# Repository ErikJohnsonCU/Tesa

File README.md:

Tesa
====

Working board design and firmware for Tesa
==========================================

Please note I mis-ordered the 10k resistors as 2k resistors, these will still work as the value of the pull-up resistors on the reset line is very flexible.

Touch pads are numbered as follows:
Power -> 1
Micro -> 2
Accel -> 3
Touch -> 4

Leds are numbered as follows:
Micro -> 0 (rgb positions to be added)
Power -> 1 (rgb positions to be added)
Accel -> 2 (rgb positions to be added)
Touch -> 3 (rgb positions to be added)
r=3,g=2,b=1

Jumper resistor functions:
R105: connects PWRIN pin + to POWER pin 1 (use this to power uC via POWER header or distribute PWRIN pin + to other boards)
RECALL: POWER pin 1 drives LEDs
R108: connects POWER pin 3 to board's Vcc (+3.3V) (use this to run uC off external +3.3V or distribute +3.3V to other boards)

Similar work by other OH designers:
http://www.ofbrooklyn.com/2014/09/6/building-pulse-bloom-biofeedback-burning-man-2014/

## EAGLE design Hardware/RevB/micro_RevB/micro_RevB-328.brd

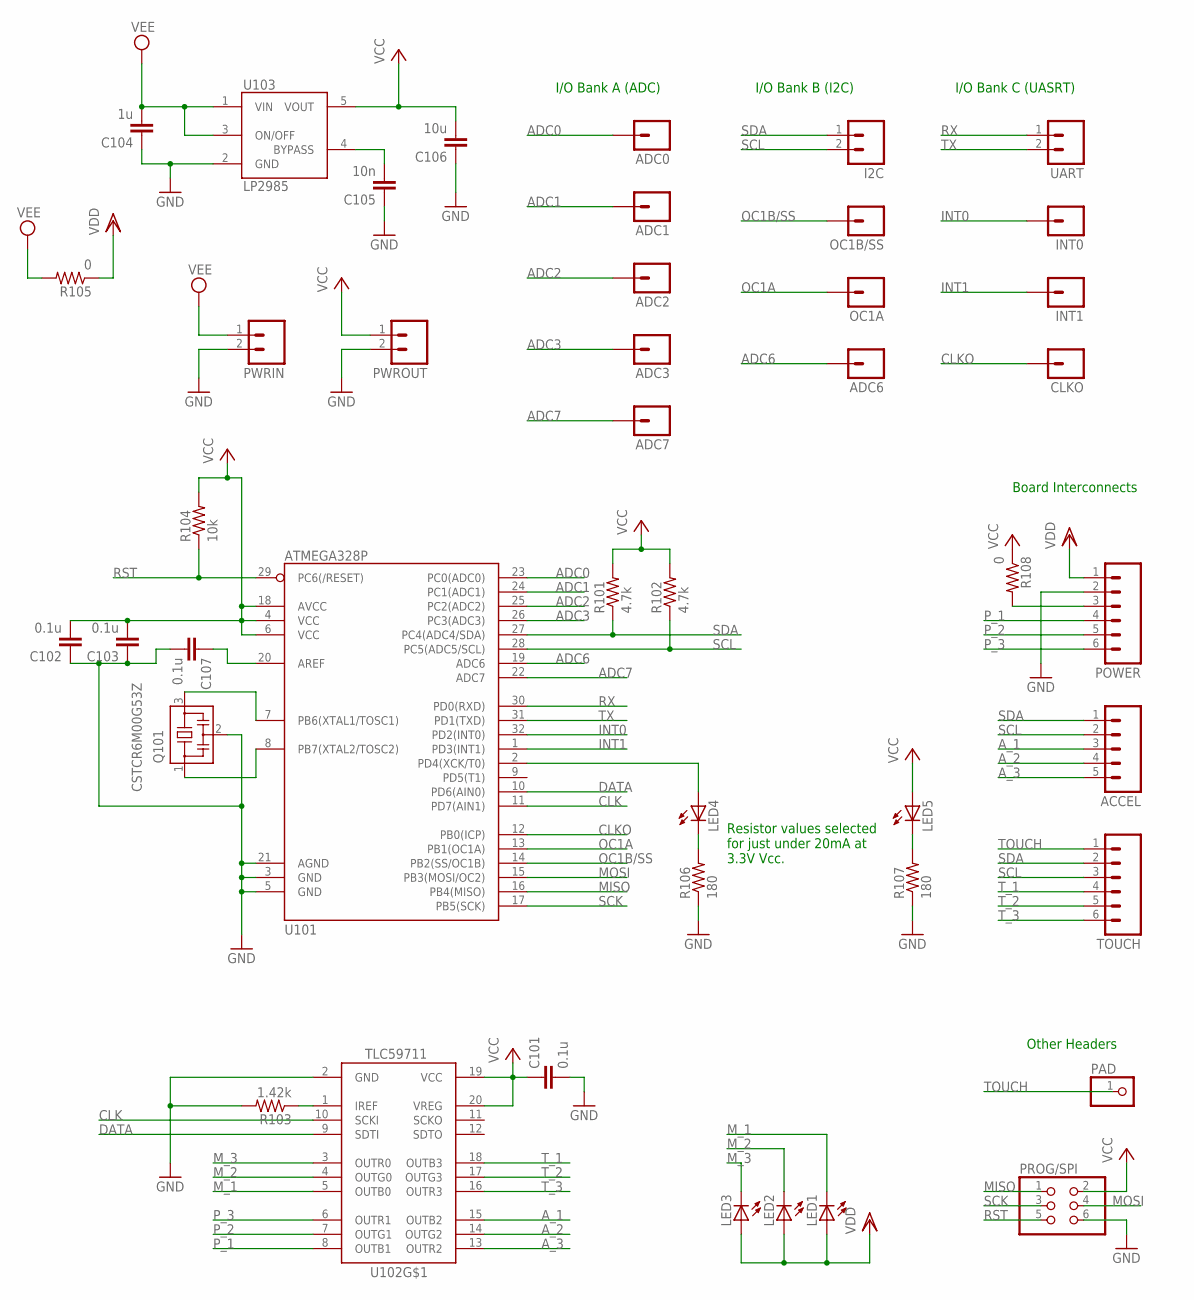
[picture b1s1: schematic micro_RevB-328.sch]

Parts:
ACCEL: M05LOCK; 1X05_LOCK
ADC0, ADC1, ADC2, ADC3, ADC6, ADC7: M01PTH; 1X01
C101, C102, C103, C107: 0.1u; C0603
C104: 1u; C0603
C105: 10n; C0603
C106: 10u; C0603
CLKO: M01PTH; 1X01
I2C: M02LOCK; 1X02_LOCK
INT0, INT1: M01PTH; 1X01
LED1, LED2, LED3: LEDP-LCC-4; P-LCC-4
LED4, LED5: LEDSML0603; SML0603
OC1A, OC1B/SS: M01PTH; 1X01
PAD: PINHD-1X1; 1X01
POWER: M06SIP_LOCK; 1X06-SIP_LOCK
PROG/SPI: PINHD-2X3; 2X03
PWRIN: M02LOCK; 1X02_LOCK
PWROUT: M02LOCK; 1X02_LOCK
Q101: CSTCR6M00G53Z; CSTCR6M
R101, R102: 4.7k; R0603
R103: 1.42k; R0603
R104: 10k; R0603
R105, R108: 0; R0603
R106, R107: 180; R0603
TOUCH: M06SIP_LOCK; 1X06-SIP_LOCK
U101: ATMEGA328P; TQFP32-08
U102: TLC59711; HTSSOP20DAP
U103: LP2985AIM5-3.3; SOT25
UART: M02LOCK; 1X02_LOCK

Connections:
ADC0: ADC0.1, U101.23 (PC0(ADC0))
ADC1: ADC1.1, U101.24 (PC1(ADC1))
ADC2: ADC2.1, U101.25 (PC2(ADC2))
ADC3: ADC3.1, U101.26 (PC3(ADC3))
ADC6: ADC6.1, U101.19 (ADC6)
ADC7: ADC7.1, U101.22 (ADC7)
A_1: ACCEL.3, U102.15 (OUTB2)
A_2: ACCEL.4, U102.14 (OUTG2)
A_3: ACCEL.5, U102.13 (OUTR2)
BYPASS: C105.2, U103.4 (BYPASS)
CLK: U101.11 (PD7(AIN1)), U102.10 (SCKI)
CLKO: CLKO.1, U101.12 (PB0(ICP))
DATA: U101.10 (PD6(AIN0)), U102.9 (SDTI)
INT0: INT0.1, U101.32 (PD2(INT0))
INT1: INT1.1, U101.1 (PD3(INT1))
MISO: PROG/SPI.1, U101.16 (PB4(MISO))
MOSI: PROG/SPI.4, U101.15 (PB3(MOSI/OC2))
M_1: LED1.C@4 (C), U102.5 (OUTB0)
M_2: LED2.C@4 (C), U102.4 (OUTG0)
M_3: LED3.C@4 (C), U102.3 (OUTR0)
N7: C101.2, C102.1, C103.1, C104.1, C105.1, C106.1, C107.2, POWER.2, PROG/SPI.6, PWRIN.2, PWROUT.2, Q101.2, R103.2, R106.1, R107.1, U101.3 (GND), U101.5 (GND), U101.21 (AGND), U102.2 (GND), U103.2 (GND)
unnamed: Q101.1, U101.8 (PB7(XTAL2/TOSC2))
unnamed: Q101.3, U101.7 (PB6(XTAL1/TOSC1))
unnamed: LED4.A, U101.2 (PD4(XCK/T0))
unnamed: R103.1, U102.1 (IREF)
unnamed: POWER.3, R108.2
unnamed: LED4.C, R106.2
unnamed: C107.1, U101.20 (AREF)
unnamed: LED5.C, R107.2
OC1A: OC1A.1, U101.13 (PB1(OC1A))
OC1B/SS: OC1B/SS.1, U101.14 (PB2(SS/OC1B))
P_1: POWER.4, U102.8 (OUTB1)
P_2: POWER.5, U102.7 (OUTG1)
P_3: POWER.6, U102.6 (OUTR1)
RST: PROG/SPI.5, R104.1, U101.29 (PC6(/RESET))
RX: U101.30 (PD0(RXD)), UART.1
SCK: PROG/SPI.3, U101.17 (PB5(SCK))
SCL: ACCEL.2, I2C.2, R102.1, TOUCH.3, U101.28 (PC5(ADC5/SCL))
SDA: ACCEL.1, I2C.1, R101.1, TOUCH.2, U101.27 (PC4(ADC4/SDA))
TOUCH: PAD.1, TOUCH.1
TX: U101.31 (PD1(TXD)), UART.2
T_1: TOUCH.4, U102.18 (OUTB3)
T_2: TOUCH.5, U102.17 (OUTG3)
T_3: TOUCH.6, U102.16 (OUTR3)
VCC: C101.1, C102.2, C103.2, C106.2, LED5.A, PROG/SPI.2, PWROUT.1, R101.2, R102.2, R104.2, R108.1, U101.4 (VCC), U101.6 (VCC), U101.18 (AVCC), U102.19 (VCC), U102.20 (VREG), U103.5 (VOUT)
VDD: LED1.A, LED2.A, LED3.A, POWER.1, R105.1
VEE: C104.2, PWRIN.1, R105.2, U103.1 (VIN), U103.3 (ON/OFF)

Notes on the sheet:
I/O Bank A (ADC)
I/O Bank B (I2C)
I/O Bank C (UASRT)
Resistor values selected for just under 20mA at 3.3V Vcc.
Board Interconnects
Other Headers

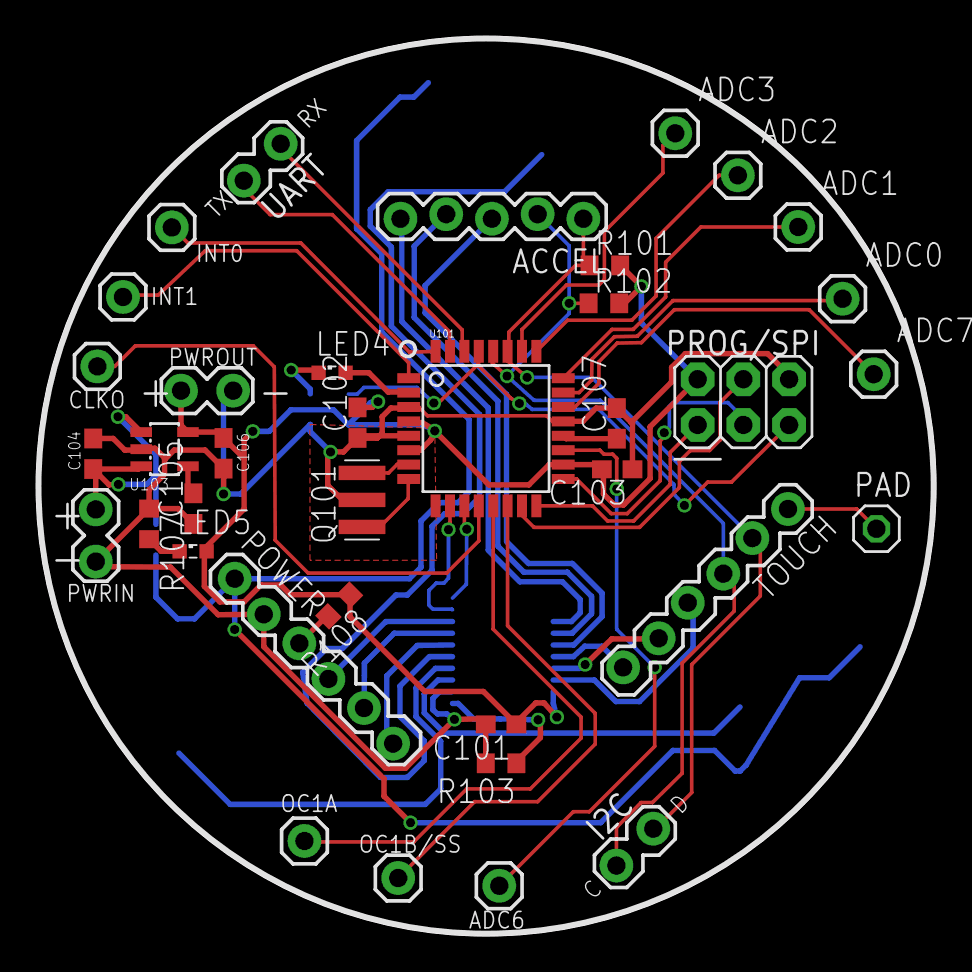
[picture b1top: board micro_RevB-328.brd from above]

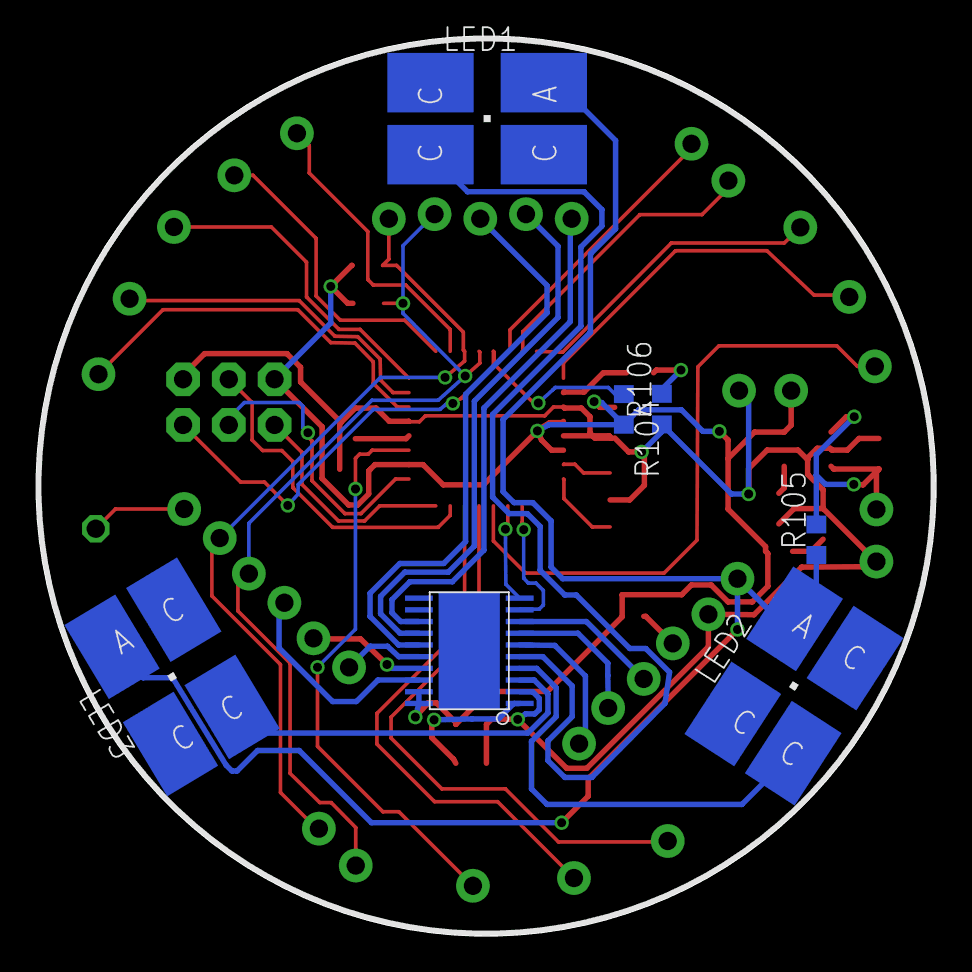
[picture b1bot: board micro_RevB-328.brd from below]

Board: 2 copper layers, 50.0 x 50.0 mm, 44 parts (7 on the bottom side), 47 nets.

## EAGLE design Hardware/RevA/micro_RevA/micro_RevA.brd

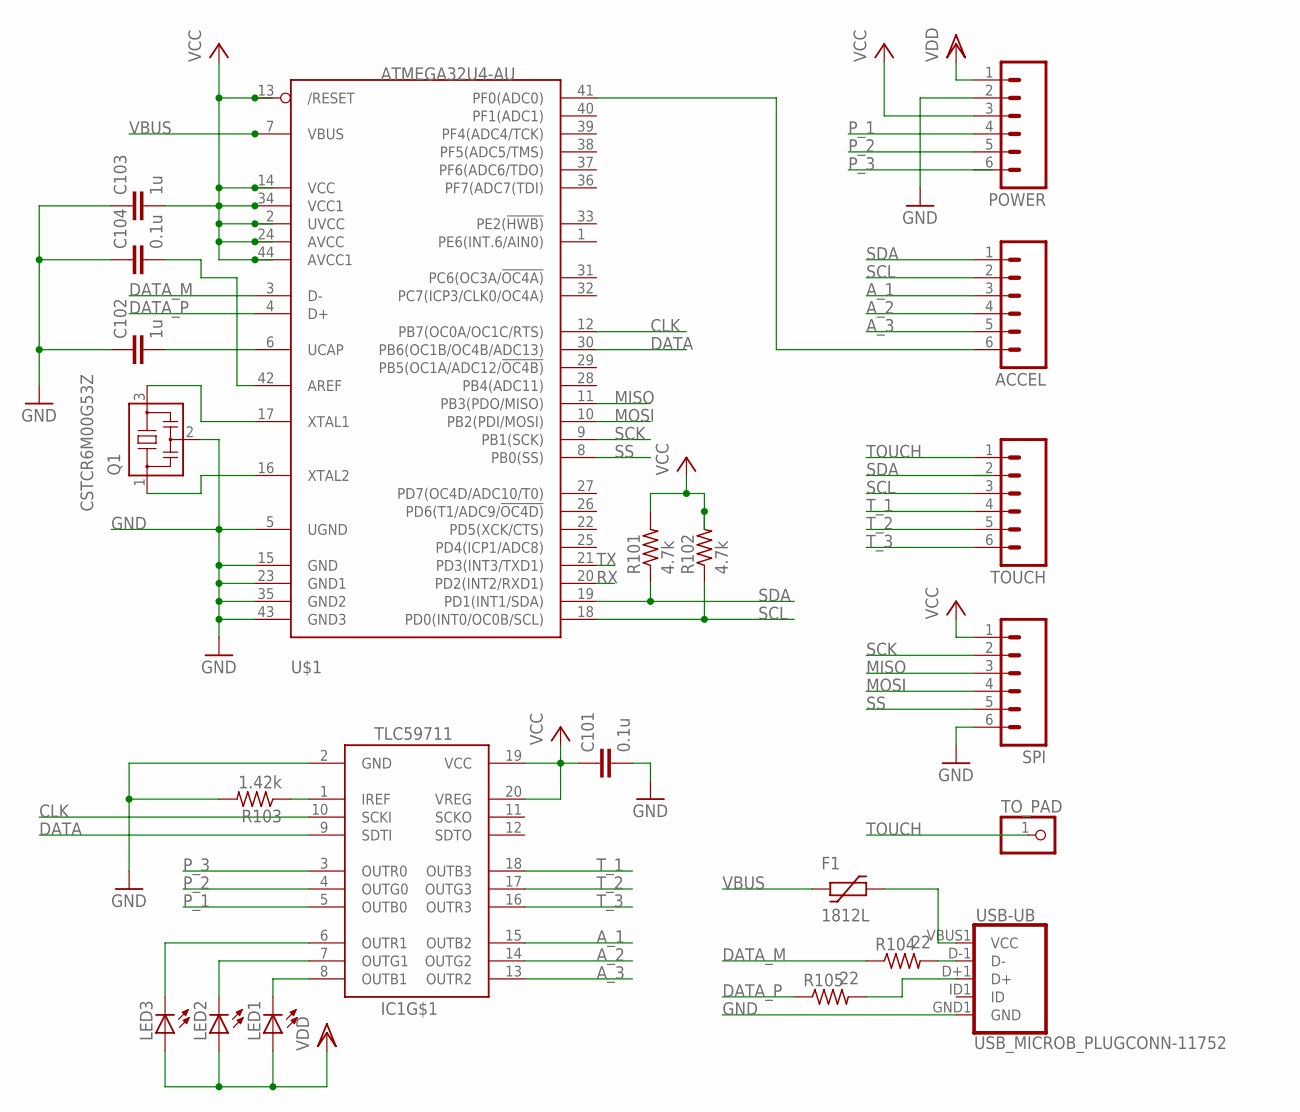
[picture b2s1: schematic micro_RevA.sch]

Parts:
ACCEL: M06SMD-STRAIGHT-ALT; 1X06_SMD_STRAIGHT_ALT
C101, C104: 0.1u; C0603
C102, C103: 1u; C0603
F1: 1812L
IC1: TLC59711; HTSSOP20DAP
LED1, LED2, LED3: LEDP-LCC-4; P-LCC-4
POWER: M06SMD-STRAIGHT-ALT; 1X06_SMD_STRAIGHT_ALT
Q1: CSTCR6M00G53Z; CSTCR6M
R101, R102: 4.7k; R0603
R103: 1.42k; R0603
R104, R105: 22; R0603
SPI: M06SMD-STRAIGHT-ALT; 1X06_SMD_STRAIGHT_ALT
TOUCH: M06SMD-STRAIGHT-ALT; 1X06_SMD_STRAIGHT_ALT
TO_PAD: PINHD-1X1; 1X01
U$1: ATMEGA32U4-AU; TQFP44
USB-UB: USB_MICROB_PLUGCONN-11752; USB-B-MICRO-SMD_V03

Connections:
A_1: ACCEL.3, IC1.15 (OUTB2)
A_2: ACCEL.4, IC1.14 (OUTG2)
A_3: ACCEL.5, IC1.13 (OUTR2)
CLK: IC1.10 (SCKI), U$1.12 (PB7(OC0A/OC1C/RTS))
DATA: IC1.9 (SDTI), U$1.30 (PB6(OC1B/OC4B/ADC13))
DATA_M: R104.1, U$1.3 (D-)
DATA_P: R105.1, U$1.4 (D+)
GND: C101.2, C102.1, C103.1, C104.1, IC1.2 (GND), POWER.2, Q1.2, R103.2, SPI.6, U$1.5 (UGND), U$1.15 (GND), U$1.23 (GND1), U$1.35 (GND2), U$1.43 (GND3), USB-UB.GND1 (GND)
MISO: SPI.3, U$1.11 (PB3(PDO/MISO))
MOSI: SPI.4, U$1.10 (PB2(PDI/MOSI))
unnamed: Q1.3, U$1.17 (XTAL1)
unnamed: Q1.1, U$1.16 (XTAL2)
unnamed: C104.2, U$1.42 (AREF)
unnamed: IC1.1 (IREF), R103.1
unnamed: IC1.6 (OUTR1), LED3.C@4 (C)
unnamed: IC1.7 (OUTG1), LED2.C@4 (C)
unnamed: IC1.8 (OUTB1), LED1.C@4 (C)
unnamed: C102.2, U$1.6 (UCAP)
unnamed: ACCEL.6, U$1.41 (PF0(ADC0))
unnamed: R104.2, USB-UB.D-1 (D-)
unnamed: R105.2, USB-UB.D+1 (D+)
unnamed: F1.P$2 (2), USB-UB.VBUS1 (VCC)
P_1: IC1.5 (OUTB0), POWER.4
P_2: IC1.4 (OUTG0), POWER.5
P_3: IC1.3 (OUTR0), POWER.6
RX: U$1.20 (PD2(INT2/RXD1))
SCK: SPI.2, U$1.9 (PB1(SCK))
SCL: ACCEL.2, R102.1, TOUCH.3, U$1.18 (PD0(INT0/OC0B/SCL))
SDA: ACCEL.1, R101.1, TOUCH.2, U$1.19 (PD1(INT1/SDA))
SS: SPI.5, U$1.8 (PB0(SS))
TOUCH: TOUCH.1, TO_PAD.1
TX: U$1.21 (PD3(INT3/TXD1))
T_1: IC1.18 (OUTB3), TOUCH.4
T_2: IC1.17 (OUTG3), TOUCH.5
T_3: IC1.16 (OUTR3), TOUCH.6
VBUS: F1.P$1 (1), U$1.7 (VBUS)
VCC: C101.1, C103.2, IC1.19 (VCC), IC1.20 (VREG), POWER.3, R101.2, R102.2, SPI.1, U$1.2 (UVCC), U$1.13 (/RESET), U$1.14 (VCC), U$1.24 (AVCC), U$1.34 (VCC1), U$1.44 (AVCC1)
VDD: LED1.A, LED2.A, LED3.A, POWER.1

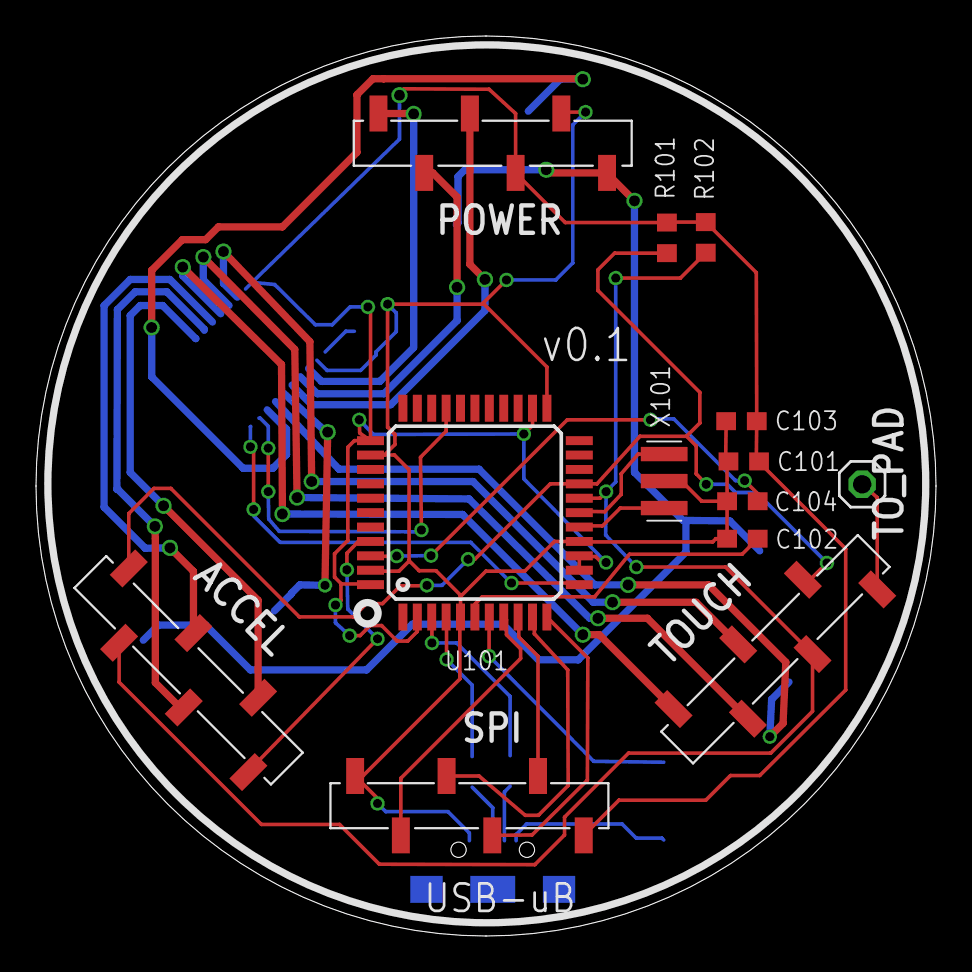
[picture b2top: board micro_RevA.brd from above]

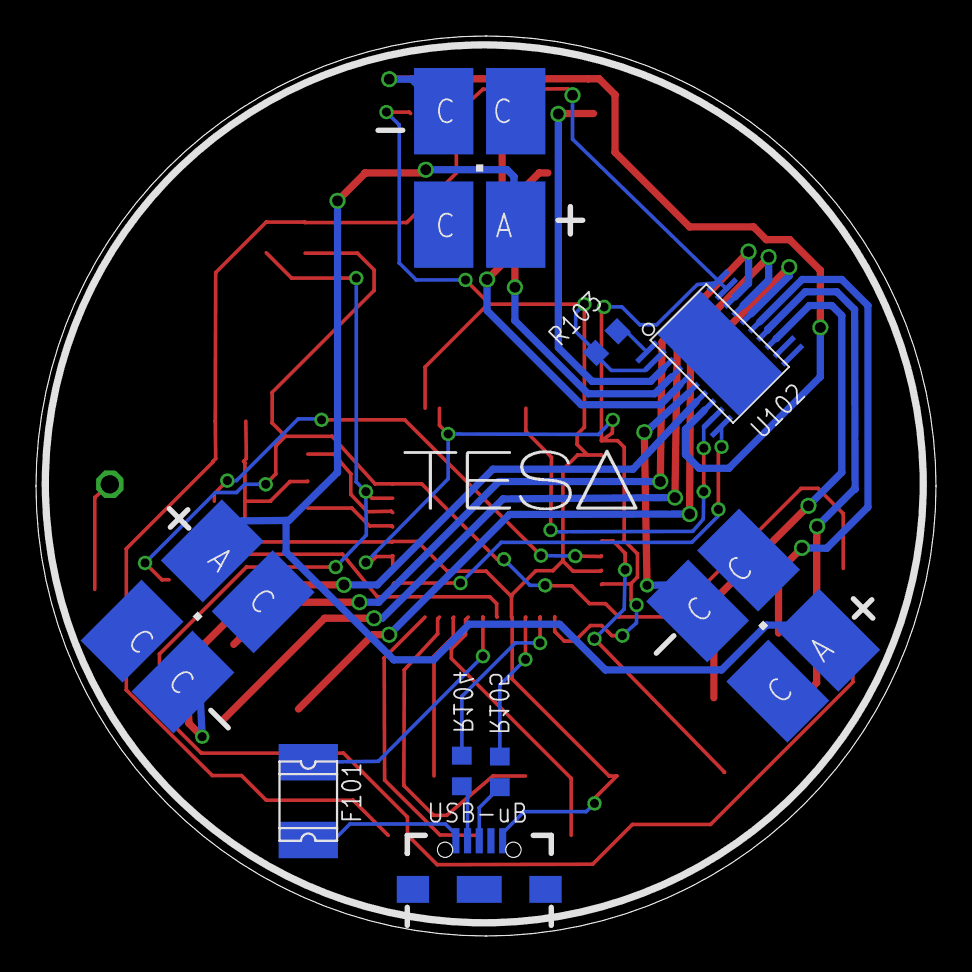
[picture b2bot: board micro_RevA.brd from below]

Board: 2 copper layers, 50.0 x 50.0 mm, 22 parts (9 on the bottom side), 36 nets.

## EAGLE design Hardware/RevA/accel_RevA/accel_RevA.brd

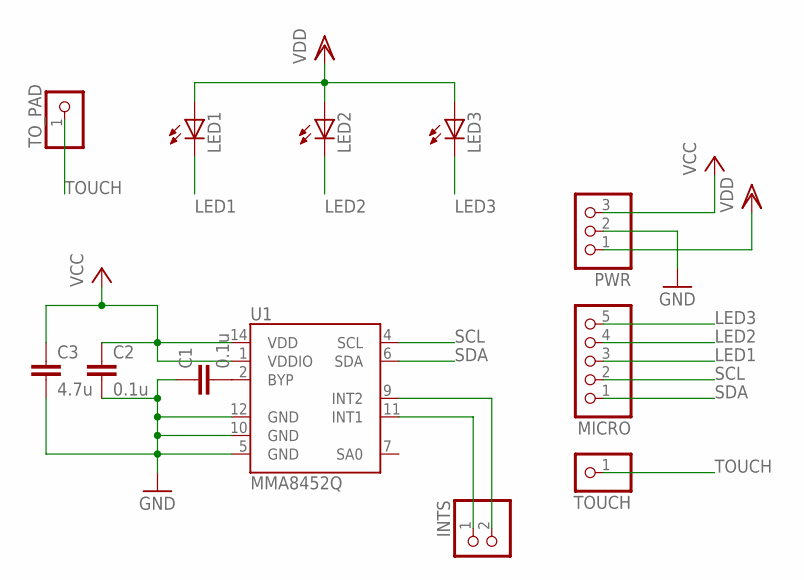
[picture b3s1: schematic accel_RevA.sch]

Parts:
C1, C2: 0.1u; C0603
C3: 4.7u; C0603
INTS: PINHD-1X2; 1X02
LED1, LED2, LED3: LEDP-LCC-4; P-LCC-4
MICRO: PINHD-1X5; 1X05
PWR: PINHD-1X3; 1X03
TOUCH: PINHD-1X1; 1X01
TO_PAD: PINHD-1X1; 1X01
U1: MMA8452Q; QFN-16_0.5MM

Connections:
GND: C1.1, C2.2, C3.2, PWR.2, U1.5 (GND), U1.10 (GND), U1.12 (GND)
LED1: LED1.C@4 (C), MICRO.3
LED2: LED2.C@4 (C), MICRO.4
LED3: LED3.C@4 (C), MICRO.5
unnamed: INTS.1, U1.11 (INT1)
unnamed: INTS.2, U1.9 (INT2)
unnamed: C1.2, U1.2 (BYP)
SCL: MICRO.2, U1.4 (SCL)
SDA: MICRO.1, U1.6 (SDA)
TOUCH: TOUCH.1, TO_PAD.1
VCC: C2.1, C3.1, PWR.3, U1.1 (VDDIO), U1.14 (VDD)
VDD: LED1.A, LED2.A, LED3.A, PWR.1

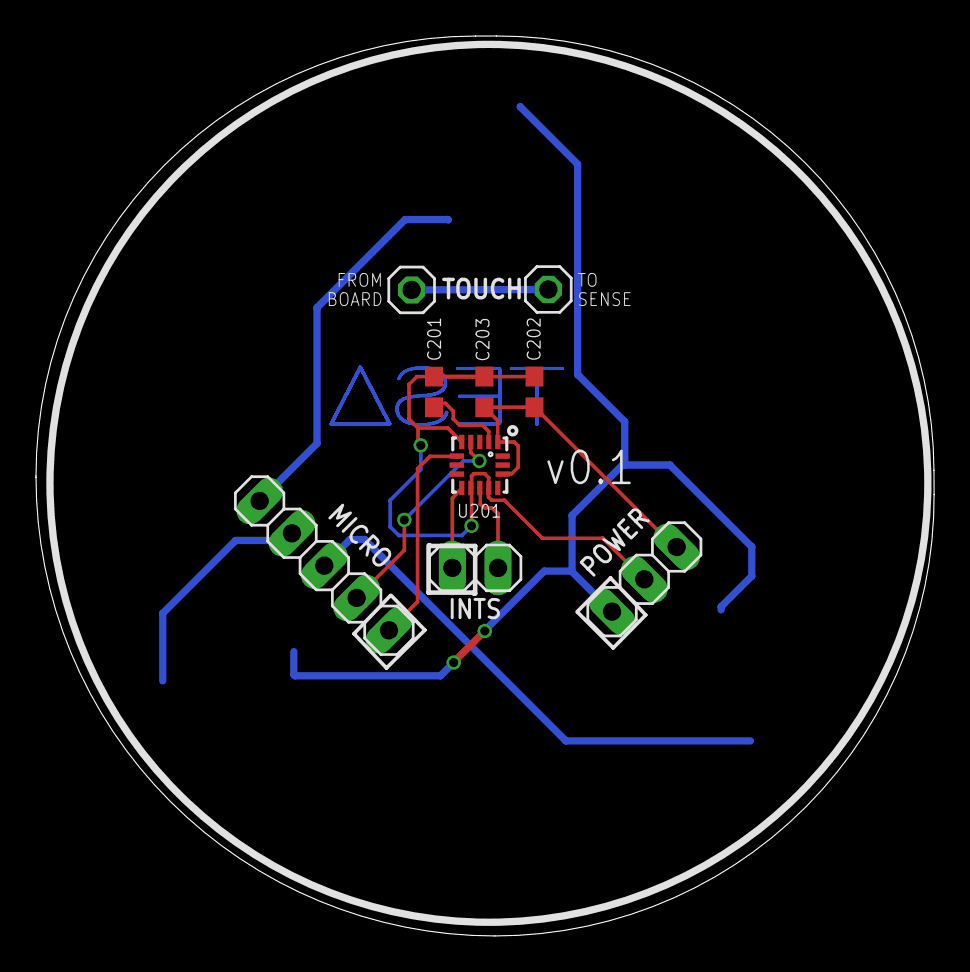
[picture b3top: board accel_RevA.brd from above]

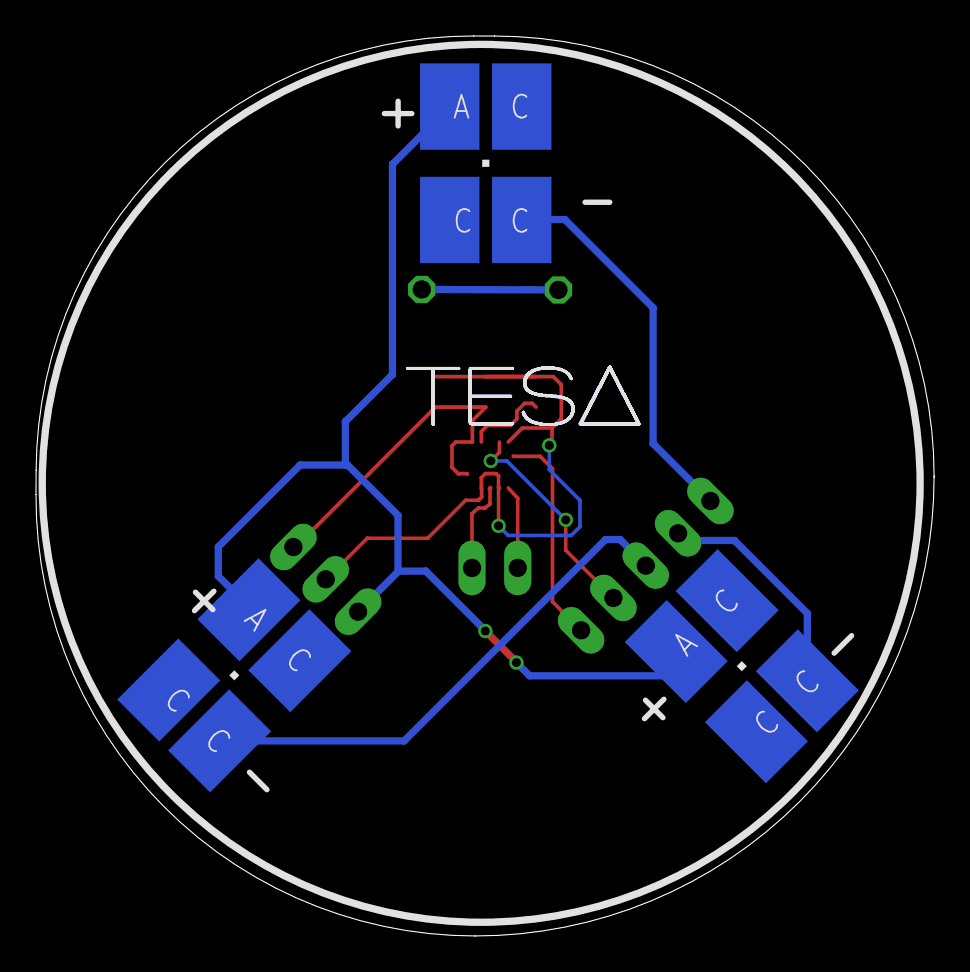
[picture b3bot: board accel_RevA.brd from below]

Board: 2 copper layers, 49.9 x 50.0 mm, 12 parts (3 on the bottom side), 12 nets.

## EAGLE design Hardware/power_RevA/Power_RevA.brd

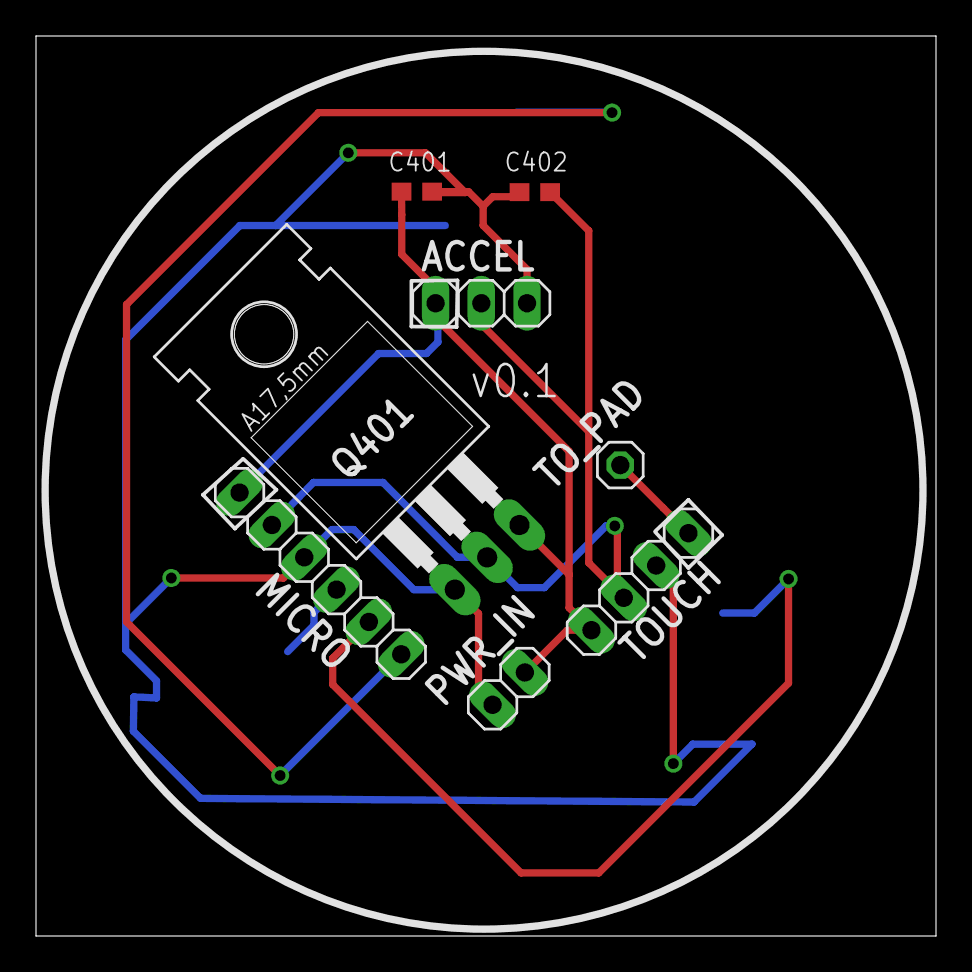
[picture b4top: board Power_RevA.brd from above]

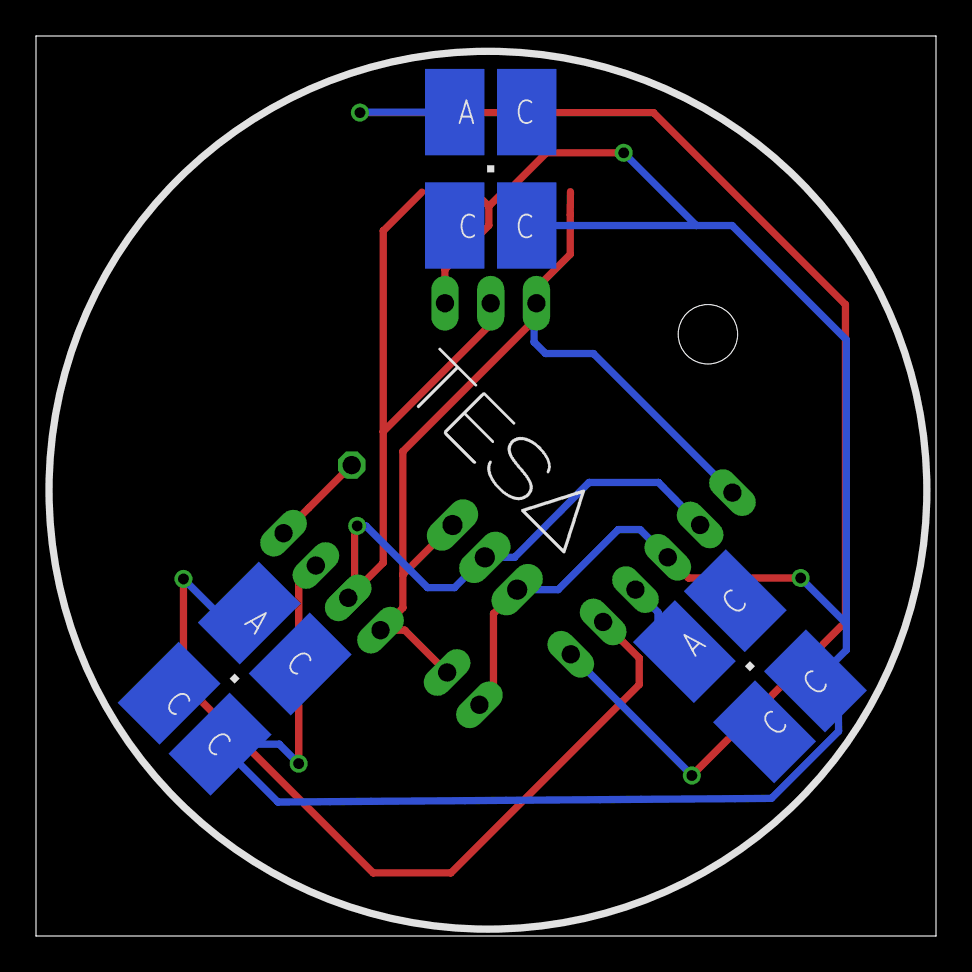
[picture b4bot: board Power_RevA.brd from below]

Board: 2 copper layers, 50.0 x 50.0 mm, 11 parts (3 on the bottom side), 7 nets.

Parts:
ACCEL: 1X03
C401: 100n; C0603
C402: 10u; C0603
LED1, LED2, LED3: P-LCC-4
MICRO: 1X06
PWR_IN: 1X02
Q401: TIP120; TO220AH
TOUCH: 1X04
TO_PAD: 1X01

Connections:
unnamed: TOUCH.4, TO_PAD.1
unnamed: ACCEL.1, C401.2, MICRO.1, PWR_IN.1, Q401.E, TOUCH.1
unnamed: ACCEL.2, C402.2, MICRO.2, Q401.C, TOUCH.2
unnamed: LED3.A, MICRO.4
unnamed: LED2.A, MICRO.5
unnamed: LED1.A, MICRO.6
unnamed: ACCEL.3, C401.1, C402.1, LED1.C@4, LED2.C@4, LED3.C@4, MICRO.3, PWR_IN.2, Q401.B, TOUCH.3

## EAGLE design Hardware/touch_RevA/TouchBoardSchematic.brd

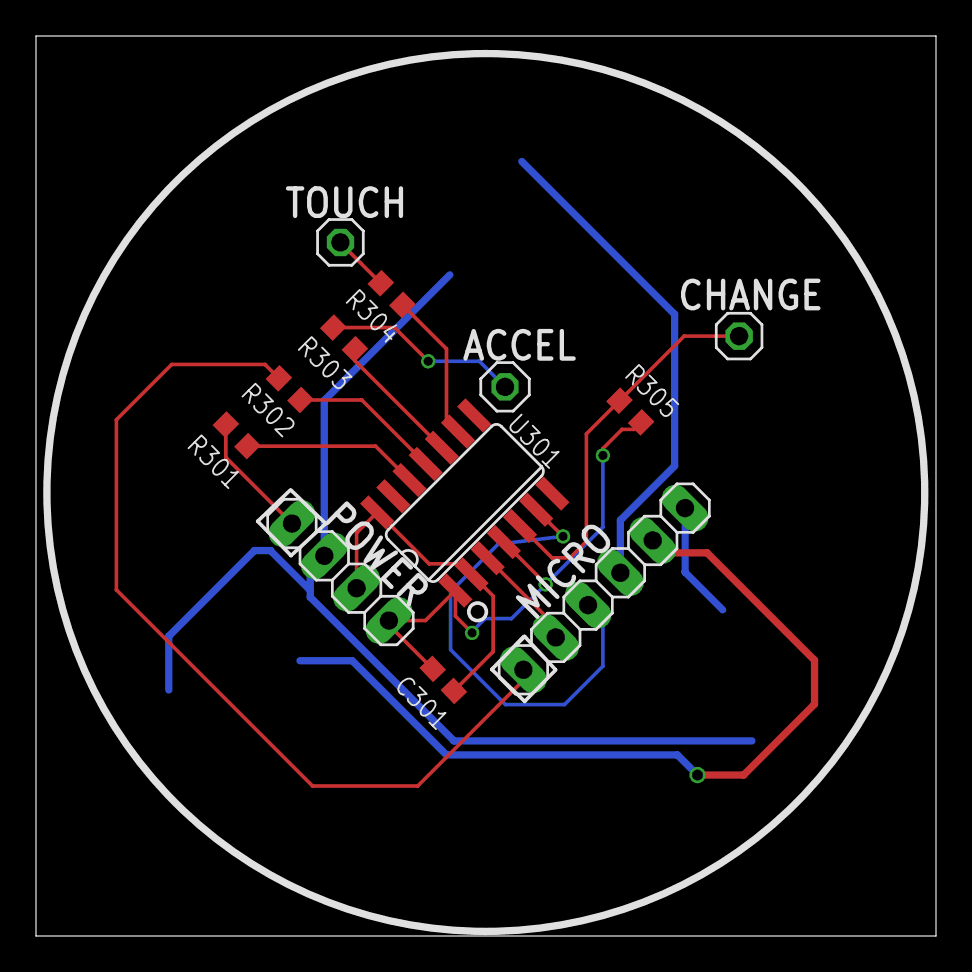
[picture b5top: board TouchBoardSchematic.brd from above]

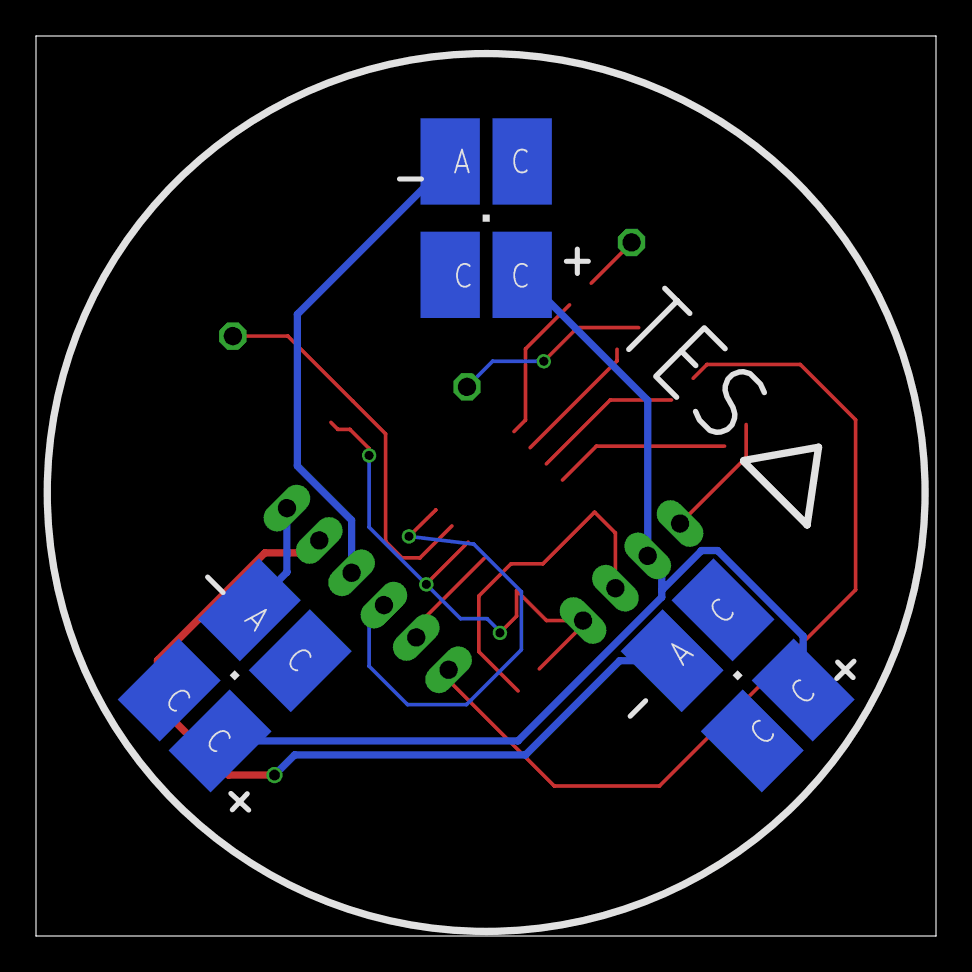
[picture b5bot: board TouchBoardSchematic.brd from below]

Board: 2 copper layers, 50.0 x 50.0 mm, 15 parts (3 on the bottom side), 17 nets.

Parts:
ACCEL: 1X01
C1: 0.1u; C0603
CHANGE_PIN: 1X01
IC1: AT42QT1070-SSU; SO14
LED1, LED2, LED3: P-LCC-4
MICRO: 1X06
PWR: 1X04
R1, R2, R3, R4, R5: 20k; R0603
TO_TOUCH: 1X01

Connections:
CHANGE: CHANGE_PIN.1, IC1.5, R5.1
GND: C1.2, IC1.2, IC1.14, PWR.3
LED1: LED1.A, MICRO.4
LED2: LED2.A, MICRO.5
LED3: LED3.A, MICRO.6
unnamed: IC1.12, R1.1
unnamed: IC1.11, R2.1
unnamed: IC1.10, R3.1
unnamed: IC1.9, R4.1
SCL: IC1.6, MICRO.3
SDA: IC1.3, MICRO.2
TOUCH1: PWR.1, R1.2
TOUCH2: MICRO.1, R2.2
TOUCH3: ACCEL.1, R3.2
TOUCH4: R4.2, TO_TOUCH.1
VCC: C1.1, IC1.1, IC1.4, PWR.4, R5.2
VDD: LED1.C@4, LED2.C@4, LED3.C@4, PWR.2

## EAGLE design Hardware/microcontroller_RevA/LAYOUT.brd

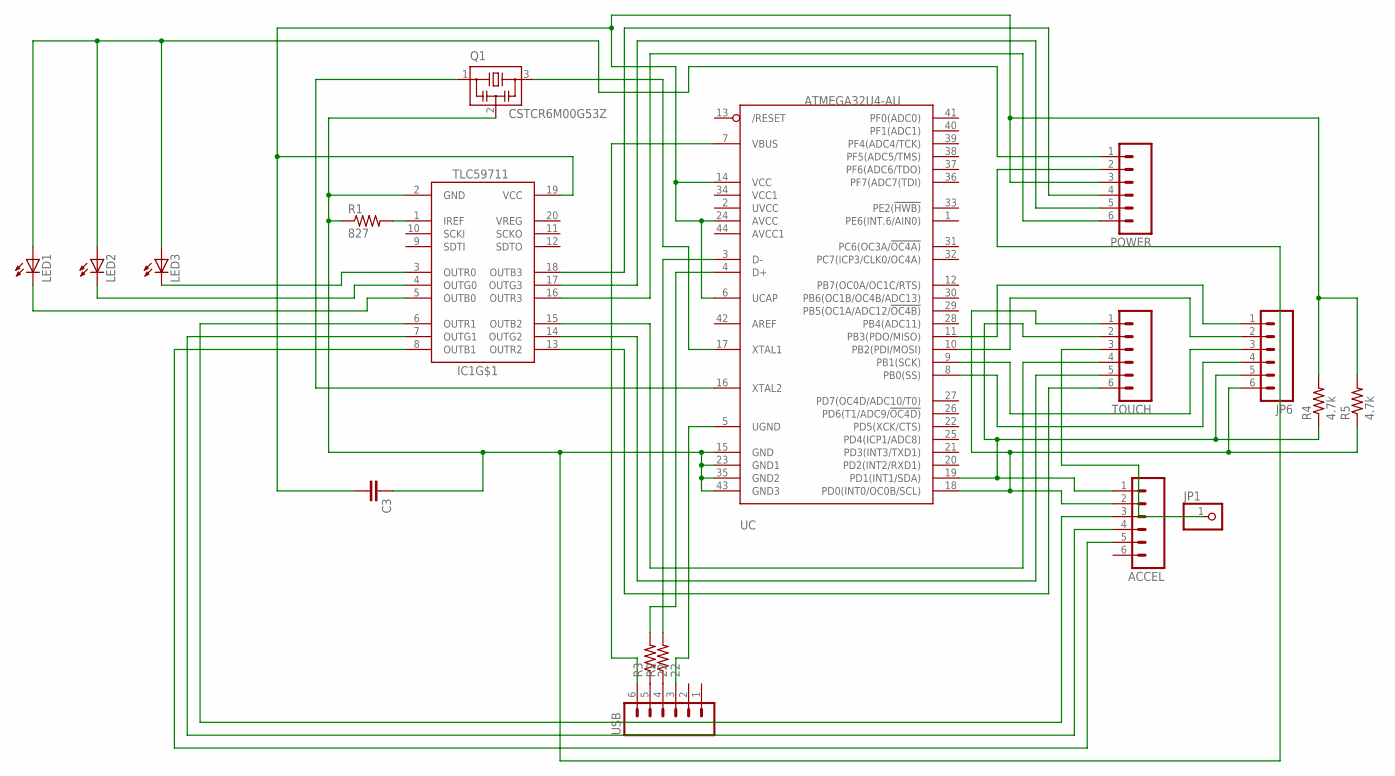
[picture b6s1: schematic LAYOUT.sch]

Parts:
ACCEL: M06SMD-STRAIGHT; 1X06_SMD_STRAIGHT
C3: CC0603; C0603
IC1: TLC59711; HTSSOP20DAP
JP1: PINHD-1X1; 1X01
JP6: M06SMD-STRAIGHT; 1X06_SMD_STRAIGHT
LED1, LED2, LED3: LEDP-LCC-4; P-LCC-4
POWER: M06SMD-STRAIGHT; 1X06_SMD_STRAIGHT
Q1: CSTCR6M00G53Z; CSTCR6M
R1: 827; R0603
R2, R3: 22; R0603
R4, R5: 4.7k; R0603
TOUCH: M06SMD-STRAIGHT; 1X06_SMD_STRAIGHT
UC: ATMEGA32U4-AU; TQFP44
USB: M06SMD-STRAIGHT; 1X06_SMD_STRAIGHT

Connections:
unnamed: C3.1, IC1.2 (GND), POWER.2, Q1.2, R1.1, UC.15 (GND), UC.23 (GND1), UC.35 (GND2), UC.43 (GND3)
unnamed: IC1.1 (IREF), R1.2
unnamed: IC1.18 (OUTB3), POWER.4
unnamed: IC1.17 (OUTG3), POWER.5
unnamed: IC1.16 (OUTR3), POWER.6
unnamed: IC1.15 (OUTB2), TOUCH.4
unnamed: IC1.14 (OUTG2), TOUCH.5
unnamed: IC1.13 (OUTR2), TOUCH.6
unnamed: ACCEL.3, IC1.6 (OUTR1)
unnamed: ACCEL.4, IC1.7 (OUTG1)
unnamed: ACCEL.5, IC1.8 (OUTB1)
unnamed: UC.7 (VBUS), USB.6
unnamed: R2.2, UC.3 (D-)
unnamed: R3.2, UC.4 (D+)
unnamed: UC.5 (UGND), USB.3
unnamed: R2.1, USB.4
unnamed: R3.1, USB.5
unnamed: Q1.3, UC.17 (XTAL1)
unnamed: Q1.1, UC.16 (XTAL2)
unnamed: JP6.2, UC.10 (PB2(PDI/MOSI))
unnamed: JP6.3, UC.9 (PB1(SCK))
unnamed: JP6.4, UC.8 (PB0(SS))
unnamed: IC1.3 (OUTR0), LED3.C@4 (C)
unnamed: IC1.4 (OUTG0), LED2.C@4 (C)
unnamed: IC1.5 (OUTB0), LED1.C@4 (C)
unnamed: LED1.A, LED2.A, LED3.A, POWER.1
unnamed: ACCEL.1, JP6.5, R4.1, TOUCH.2, UC.19 (PD1(INT1/SDA))
unnamed: ACCEL.2, JP6.6, R5.1, TOUCH.1, UC.18 (PD0(INT0/OC0B/SCL))
unnamed: JP6.1, UC.11 (PB3(PDO/MISO))
unnamed: JP1.1, TOUCH.3
unnamed: C3.2, IC1.19 (VCC), POWER.3, R4.2, R5.2, UC.6 (UCAP), UC.14 (VCC), UC.24 (AVCC)

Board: 2 copper layers, 18 parts (5 on the bottom side), 31 nets, no tracks yet.

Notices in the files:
parts and their libraries:
SparkFun-Sensors: Licensing: Creative Commons ShareAlike 4.0 International - https://creativecommons.org/licenses/by-sa/4.0
